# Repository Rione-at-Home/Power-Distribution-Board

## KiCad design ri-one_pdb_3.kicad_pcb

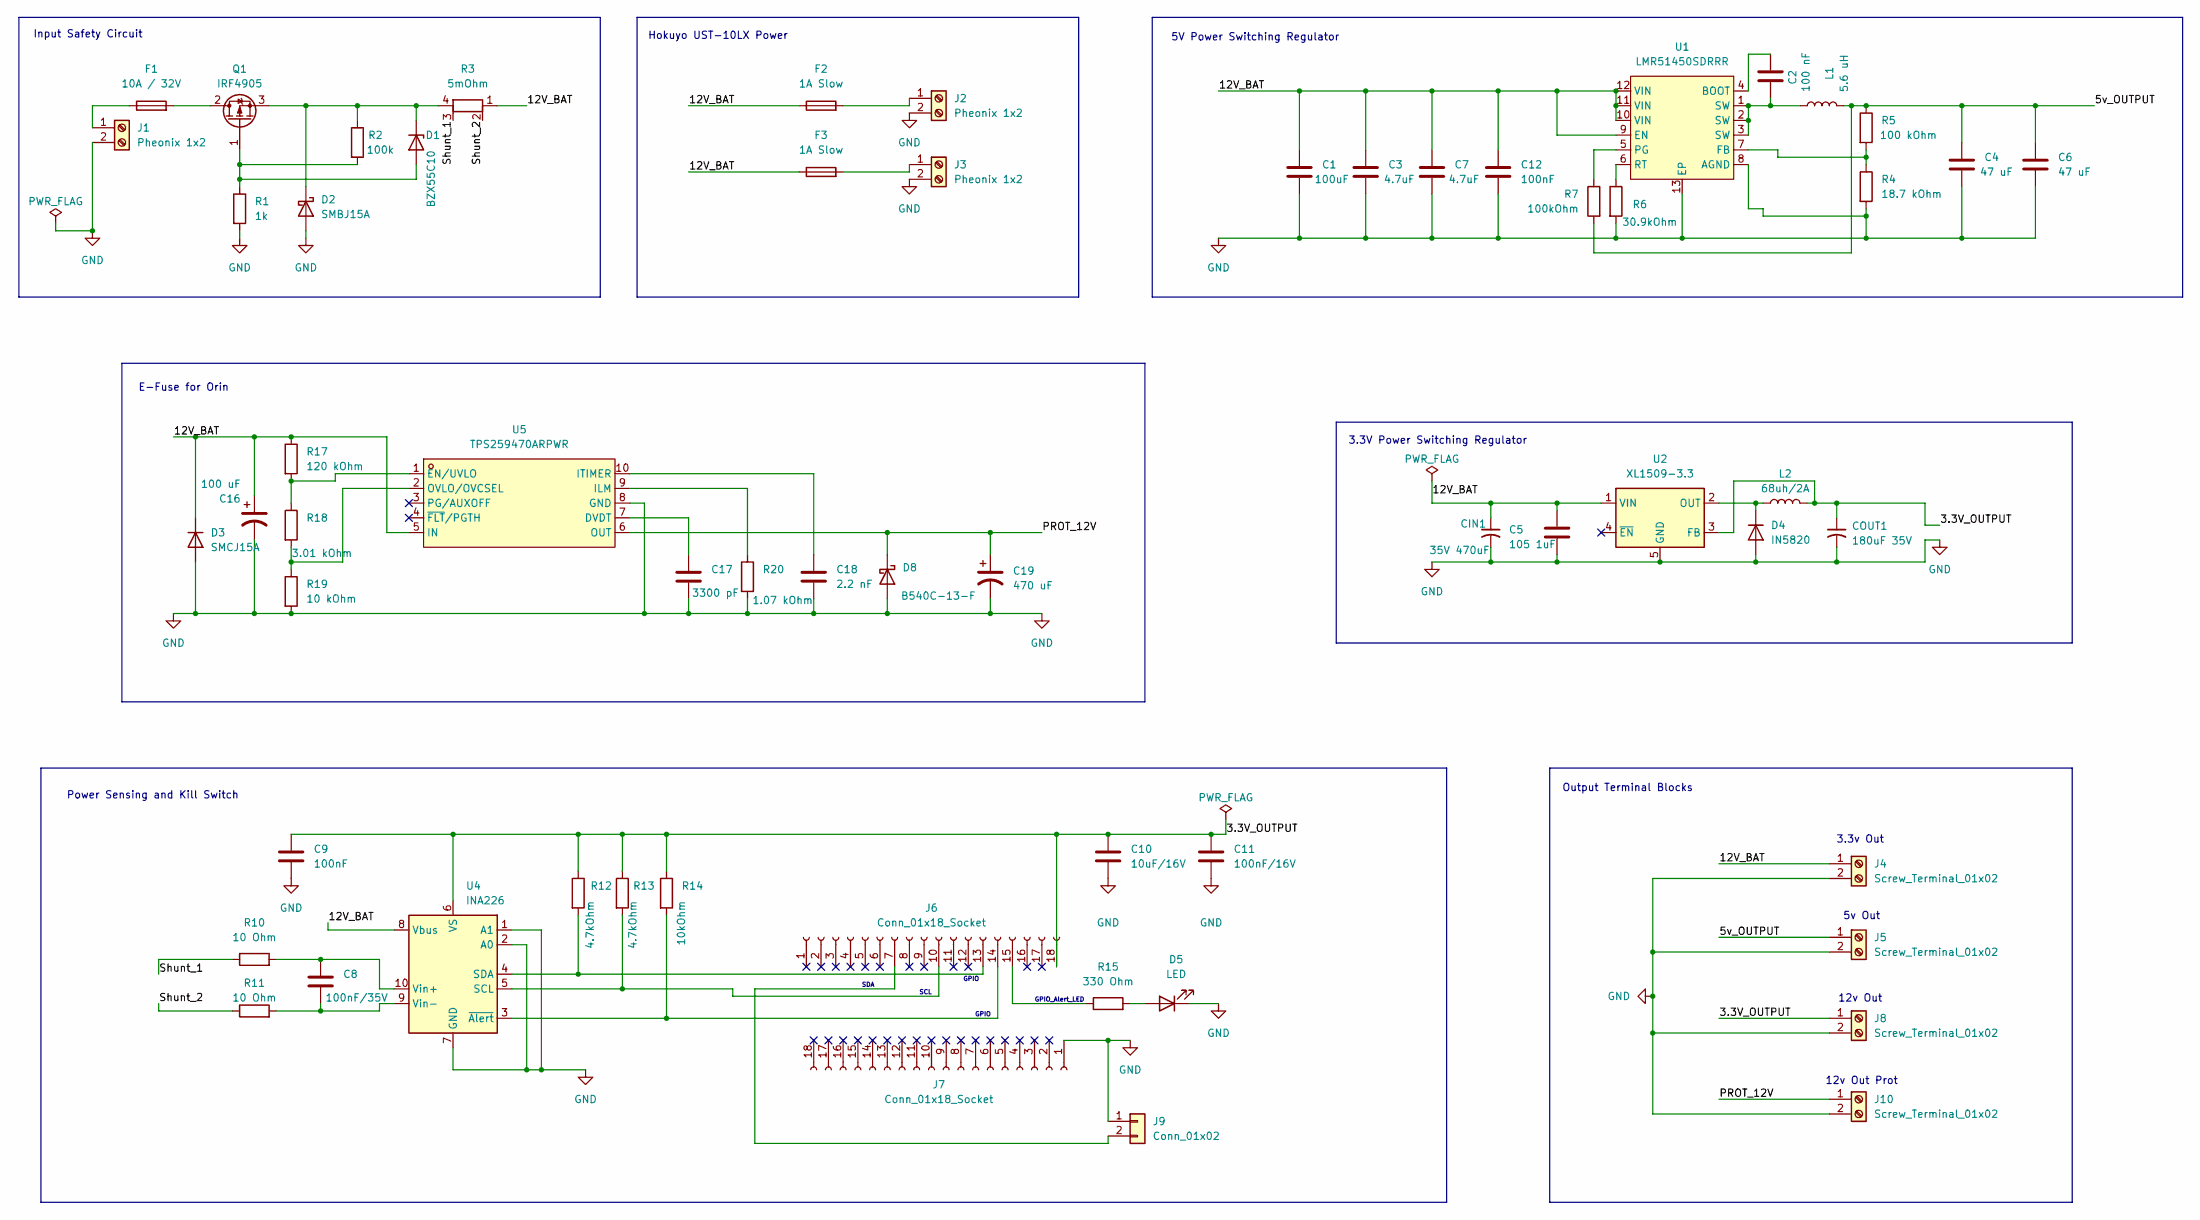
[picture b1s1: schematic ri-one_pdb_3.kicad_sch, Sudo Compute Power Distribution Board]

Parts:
C1: 100uF; CP_Elec_10x10.5
C2: 100 nF; C_0603_1608Metric
C3, C7: 4.7uF; C_1206_3216Metric
C4, C6: 47 uF; C_1210_3225Metric
C5: 105 1uF; C_0805_2012Metric
C8: 100nF/35V; C_0603_1608Metric
C9, C12: 100nF; C_0603_1608Metric
C10: 10uF/16V; C_0805_2012Metric
C11: 100nF/16V; C_0603_1608Metric
C16: 100 uF; CP_Elec_10x10.5
C17: 3300 pF; C_0603_1608Metric
C18: 2.2 nF; C_0603_1608Metric
C19: 470 uF; CP_Elec_10x10.5
CIN1: 35V 470uF; CP_Radial_D10.0mm_P5.00mm
COUT1: 180uF 35V; CP_Radial_D8.0mm_P3.50mm
D1: BZX55C10; D_DO-35_SOD27_P7.62mm_Horizontal
D2: SMBJ15A; D_SMB
D3: SMCJ15A; D_SMC
D4: IN5820; D_DO-201AD_P15.24mm_Horizontal
D5: LED; LED_0805_2012Metric
D8: B540C-13-F; D_SMC
F1: 10A / 32V; Fuse_1206_3216Metric
F2, F3: 1A Slow; Fuse_0402_1005Metric
J1: Pheonix 1x2; TerminalBlock_Phoenix_MKDS-1,5-2-5.08_1x02_P5.08mm_Horizont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
J2, J3: Pheonix 1x2; TerminalBlock_Phoenix_PTSM-0,5-2-2.5-V-THR_1x02_P2.50mm_Ver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
J4, J5, J8, J10: Screw_Terminal_01x02; TerminalBlock_Phoenix_PTSM-0,5-2-2.5-V-THR_1x02_P2.50mm_Ver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
J6, J7: Conn_01x18_Socket; PinSocket_1x18_P2.54mm_Vertical
J9: Conn_01x02; TerminalBlock_Phoenix_PTSM-0,5-2-2.5-V-THR_1x02_P2.50mm_Ver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
L1: 5.6 uH; IND-SMD_L8.5-W8.0_PCC-M0854M
L2: 68uh/2A; L_Bourns_SRR1210A
Q1: IRF4905; TO-220-3_Vertical
R1: 1k; R_0805_2012Metric
R2: 100k; R_0805_2012Metric
R3: 5mOhm; R_Shunt_Isabellenhuette_BVR4026
R4: 18.7 kOhm; R_0805_2012Metric
R5: 100 kOhm; R_0805_2012Metric
R6: 30.9kOhm; R_0805_2012Metric
R7: 100kOhm; R_0805_2012Metric
R10, R11: 10 Ohm; R_0805_2012Metric
R12, R13: 4.7kOhm; R_0805_2012Metric
R14: 10kOhm; R_0805_2012Metric
R15: 330 Ohm; R_0805_2012Metric
R17: 120 kOhm; R_0805_2012Metric
R18: 3.01 kOhm; R_0805_2012Metric
R19: 10 kOhm; R_0805_2012Metric
R20: 1.07 kOhm; R_0805_2012Metric
U1: LMR51450SDRRR; WSON-12_L3.0-W3.0-P0.50-TL-EP-2; MPN LMR51450SDRRR; LCSC Part C6890985
U2: XL1509-3.3; SOIC-8_3.9x4.9mm_P1.27mm
U4: INA226; TSSOP-10_3x3mm_P0.5mm
U5: TPS259470ARPWR; VQFN-10_L2.0-W2.0-P0.45-TL

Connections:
/3.3V_OUTPUT: C9.1, C10.1, C11.1, COUT1.1, J6.18, J8.1, L2.2, R12.1, R13.1, R14.1, U2.3 (FB), U4.6 (VS)
/5v_OUTPUT: C4.1, C6.1, J5.1, L1.2, R5.1, R7.2
/12V_BAT: C1.1, C3.1, C5.1, C7.1, C12.1, C16.1, CIN1.1, D3.1 (K), F2.1, F3.1, J4.1, R3.1, R17.1, U1.9 (EN), U1.10 (VIN), U1.11 (VIN), U1.12 (VIN), U2.1 (VIN), U4.8 (Vbus), U5.5 (IN)
/PROT_12V: C19.1, D8.1 (K), J10.1, U5.6 (OUT)
/Shunt_1: R3.3, R10.1
/Shunt_2: R3.2, R11.1
GND: C1.2, C3.2, C4.2, C5.2, C6.2, C7.2, C9.2, C10.2, C11.2, C12.2, C16.2, C17.2, C18.2, C19.2, CIN1.2, COUT1.2, D2.2 (A), D3.2 (A), D4.2 (A), D5.1 (K), D8.2 (A), J1.2, J2.2, J3.2, J4.2, J5.2, J7.1 (Pin_1_1), J8.2, J9.1, J10.2, R1.2, R4.2, R6.2, R19.2, R20.2, U1.8 (AGND), U1.13 (EP), U2.5 (GND), U2.6 (GND), U2.7 (GND), U2.8 (GND), U4.1 (A1), U4.2 (A0), U4.7 (GND), U5.8 (GND); also elsewhere on the board
unnamed: C2.2, L1.1, U1.1 (SW), U1.2 (SW), U1.3 (SW)
unnamed: D1.2 (A), Q1.1 (G), R1.1, R2.2
unnamed: D1.1 (K), D2.1 (K), Q1.3 (S), R2.1, R3.4
unnamed: D4.1 (K), L2.1, U2.2 (OUT)
unnamed: D5.2 (A), R15.2
unnamed: F1.1, J1.1
unnamed: F2.2, J2.1
unnamed: F3.2, J3.1
unnamed: J6.7, J9.2
unnamed: J6.10, R13.2, U4.5 (SCL)
unnamed: J6.13, R12.2, U4.4 (SDA)
unnamed: J6.14, R14.2, U4.3 (~Alert)
unnamed: J6.15, R15.1
unnamed 21: F1.2, Q1.2 (D); also elsewhere on the board
unnamed: C2.1, U1.4 (BOOT)
unnamed: R4.1, R5.2, U1.7 (FB)
unnamed: R7.1, U1.5 (PG)
unnamed: R6.1, U1.6 (RT)
unnamed: C8.1, R10.2, U4.10 (Vin+)
unnamed: C8.2, R11.2, U4.9 (Vin-)
unnamed: C17.1, U5.7 (DVDT)
unnamed: R17.2, R18.1, U5.1 (EN/UVLO)
unnamed: R20.1, U5.9 (ILM)
unnamed: C18.1, U5.10 (ITIMER)
unnamed: R18.2, R19.1, U5.2 (OVLO/OVCSEL)

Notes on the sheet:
Power Sensing and Kill Switch
GPIO_Alert_LED
E-Fuse for Orin
GPIO
5V Power Switching Regulator
3.3V Power Switching Regulator
SDA
12v Out
Input Safety Circuit
5v Out
SCL
12v Out Prot
3.3v Out
Hokuyo UST-10LX Power
Output Terminal Blocks

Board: 4 copper layers, 61 parts (0 on the bottom side), 32 nets, no tracks yet.

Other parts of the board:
12V_IN: Battery_Input; TerminalBlock_Phoenix_MKDS-1,5-2-5.08_1x02_P5.08mm_Horizont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
F10A: 10A / 32V; Fuse_1206_3216Metric

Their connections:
GND: 12V_IN.2; also elsewhere on the board
unnamed: 12V_IN.1, F10A.1
unnamed 21: F10A.2; also elsewhere on the board
